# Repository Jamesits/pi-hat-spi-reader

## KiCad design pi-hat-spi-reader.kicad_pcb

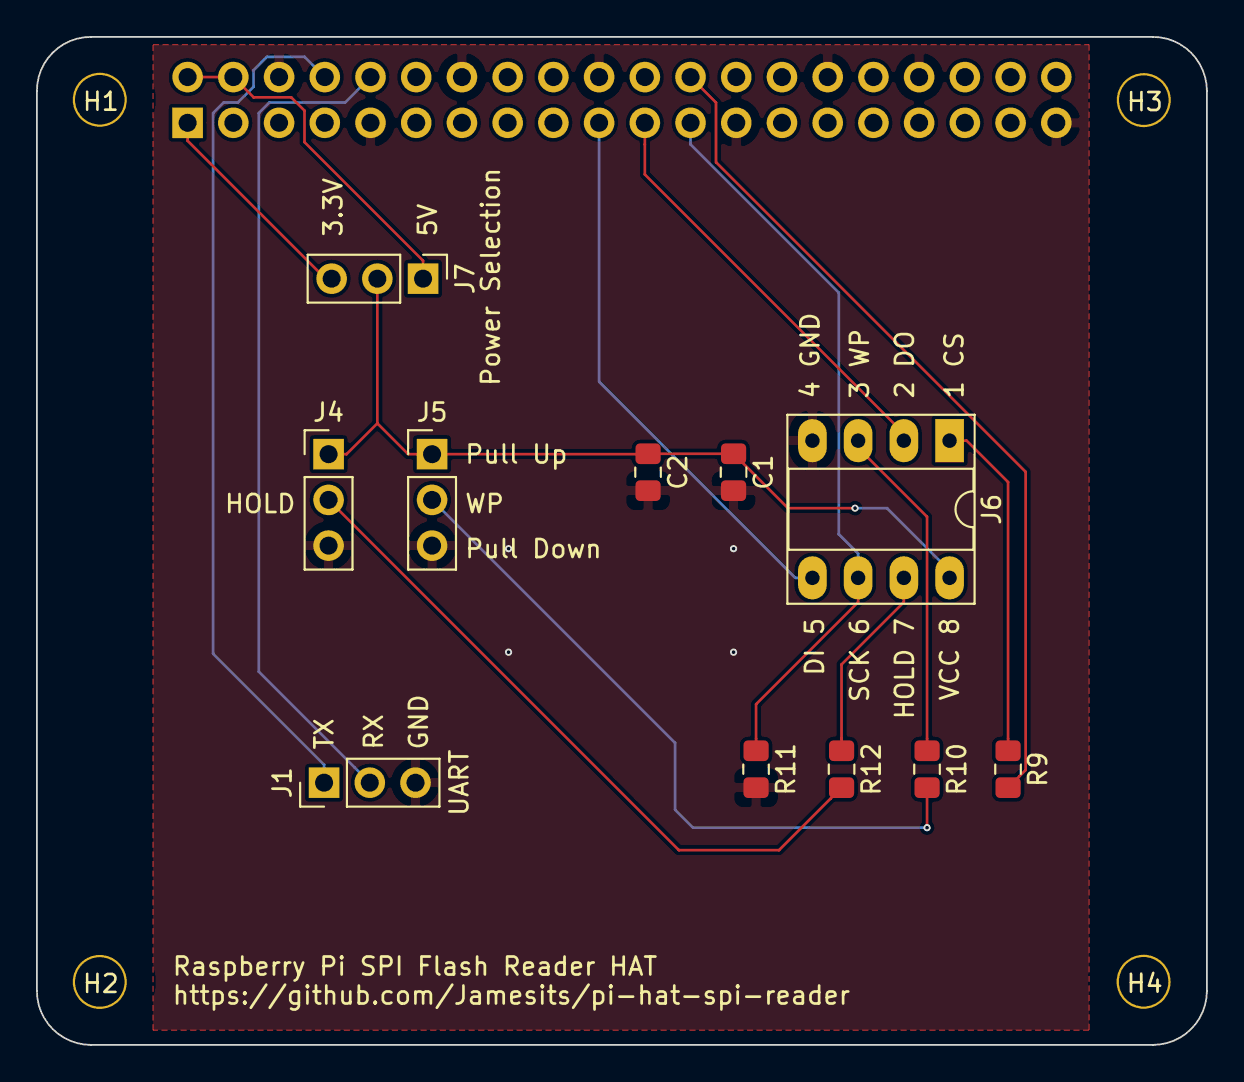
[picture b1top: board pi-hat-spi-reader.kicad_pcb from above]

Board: 2 copper layers, 65.0 x 56.0 mm, 16 parts (1 on the bottom side), 15 nets.

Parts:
C1, C2: 4.7uF; C_0805_2012Metric_Pad1.15x1.40mm_HandSolder
H1, H2, H3, H4: 3mm_Mounting_Hole; NPTH_3mm_ID
J1, J4, J5, J7: Conn_01x03_Male; PinHeader_1x03_P2.54mm_Vertical
J2: 40HAT; PinSocket_2x20_P2.54mm_Vertical
J6: Conn_02x04_Counter_Clockwise; DIP-8_W7.62mm_Socket_LongPads
R9, R12: 10K; R_0805_2012Metric_Pad1.15x1.40mm_HandSolder
R10: 10k; R_0805_2012Metric_Pad1.15x1.40mm_HandSolder
R11: 100K; R_0805_2012Metric_Pad1.15x1.40mm_HandSolder

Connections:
+3V3: J2.1, J7.3
+5V: J2.2, J2.4, J7.1
CS: J2.24, R9.2
DI: J2.19, J6.5
DO: J2.21, J6.2
GND: C1.2, C2.2, J1.3, J2.6, J2.9, J2.14, J2.20, J2.25, J2.30, J2.34, J2.39, J4.3, J5.3, J6.4, R11.2
HOLD: J4.2, R12.2
unnamed: J6.1, R9.1
unnamed: J6.3, R10.1
unnamed: J6.7, R12.1
SCK: J2.23, J6.6, R11.1
SPI_PWR: C1.1, C2.1, J4.1, J5.1, J6.8, J7.2
Serial_RX: J1.2, J2.10
Serial_TX: J1.1, J2.8
WP: J5.2, R10.2
